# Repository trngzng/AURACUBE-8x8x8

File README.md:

# AURACUBE-8x8x8
RGB LED CUBE 8X8X8

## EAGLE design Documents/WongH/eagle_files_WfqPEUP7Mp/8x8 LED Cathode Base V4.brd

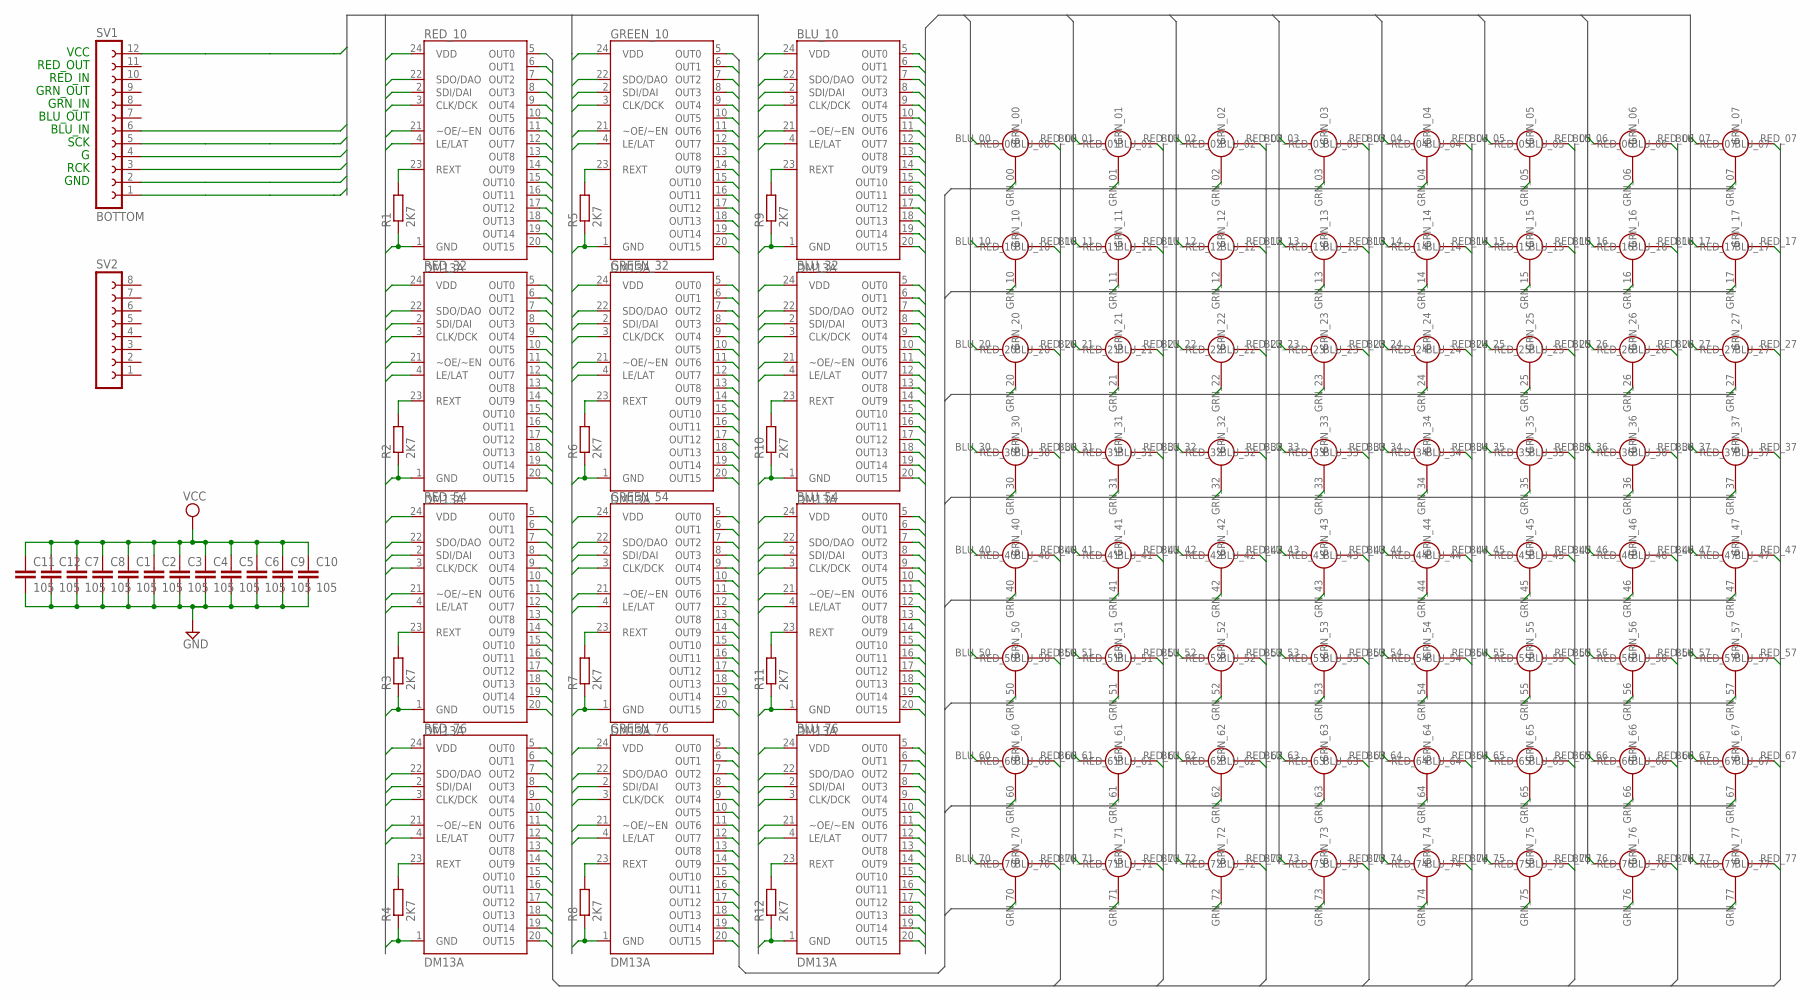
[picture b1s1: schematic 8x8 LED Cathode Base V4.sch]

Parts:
BLU_10, BLU_32, BLU_54, BLU_76: DM13A; DIL24-3
C1, C2, C3, C4, C5, C6, C7, C8, C9, C10, C11, C12: 105; C1206
GREEN_10, GREEN_32, GREEN_54, GREEN_76: DM13A; DIL24-3
R1, R2, R3, R4, R5, R6, R7, R8, R9, R10, R11, R12: 2K7; R1206
RED_10, RED_32, RED_54, RED_76: DM13A; DIL24-3
SV1: BOTTOM; FE12
SV2: FE08-1; FE08
U$1: 8X8_RGB_COLUMN; 8X8_RGB_LED_120

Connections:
BLANK: BLU_10.21 (~OE/~EN), BLU_32.21 (~OE/~EN), BLU_54.21 (~OE/~EN), BLU_76.21 (~OE/~EN), GREEN_10.21 (~OE/~EN), GREEN_32.21 (~OE/~EN), GREEN_54.21 (~OE/~EN), GREEN_76.21 (~OE/~EN), RED_10.21 (~OE/~EN), RED_32.21 (~OE/~EN), RED_54.21 (~OE/~EN), RED_76.21 (~OE/~EN), SV1.4
BLU_00: BLU_10.5 (OUT0), U$1.BLU_00
BLU_01: BLU_10.6 (OUT1), U$1.BLU_01
BLU_02: BLU_10.7 (OUT2), U$1.BLU_02
BLU_03: BLU_10.8 (OUT3), U$1.BLU_03
BLU_04: BLU_10.9 (OUT4), U$1.BLU_04
BLU_05: BLU_10.10 (OUT5), U$1.BLU_05
BLU_06: BLU_10.11 (OUT6), U$1.BLU_06
BLU_07: BLU_10.12 (OUT7), U$1.BLU_07
BLU_10: BLU_10.13 (OUT8), U$1.BLU_10
BLU_11: BLU_10.14 (OUT9), U$1.BLU_11
BLU_12: BLU_10.15 (OUT10), U$1.BLU_12
BLU_13: BLU_10.16 (OUT11), U$1.BLU_13
BLU_14: BLU_10.17 (OUT12), U$1.BLU_14
BLU_15: BLU_10.18 (OUT13), U$1.BLU_15
BLU_16: BLU_10.19 (OUT14), U$1.BLU_16
BLU_17: BLU_10.20 (OUT15), U$1.BLU_17
BLU_20: BLU_32.5 (OUT0), U$1.BLU_20
BLU_21: BLU_32.6 (OUT1), U$1.BLU_21
BLU_22: BLU_32.7 (OUT2), U$1.BLU_22
BLU_23: BLU_32.8 (OUT3), U$1.BLU_23
BLU_24: BLU_32.9 (OUT4), U$1.BLU_24
BLU_25: BLU_32.10 (OUT5), U$1.BLU_25
BLU_26: BLU_32.11 (OUT6), U$1.BLU_26
BLU_27: BLU_32.12 (OUT7), U$1.BLU_27
BLU_30: BLU_32.13 (OUT8), U$1.BLU_30
BLU_31: BLU_32.14 (OUT9), U$1.BLU_31
BLU_32: BLU_32.15 (OUT10), U$1.BLU_32
BLU_32_DATA: BLU_10.22 (SDO/DAO), BLU_32.2 (SDI/DAI)
BLU_33: BLU_32.16 (OUT11), U$1.BLU_33
BLU_34: BLU_32.17 (OUT12), U$1.BLU_34
BLU_35: BLU_32.18 (OUT13), U$1.BLU_35
BLU_36: BLU_32.19 (OUT14), U$1.BLU_36
BLU_37: BLU_32.20 (OUT15), U$1.BLU_37
BLU_40: BLU_54.5 (OUT0), U$1.BLU_40
BLU_41: BLU_54.6 (OUT1), U$1.BLU_41
BLU_42: BLU_54.7 (OUT2), U$1.BLU_42
BLU_43: BLU_54.8 (OUT3), U$1.BLU_43
BLU_44: BLU_54.9 (OUT4), U$1.BLU_44
BLU_45: BLU_54.10 (OUT5), U$1.BLU_45
BLU_46: BLU_54.11 (OUT6), U$1.BLU_46
BLU_47: BLU_54.12 (OUT7), U$1.BLU_47
BLU_50: BLU_54.13 (OUT8), U$1.BLU_50
BLU_51: BLU_54.14 (OUT9), U$1.BLU_51
BLU_52: BLU_54.15 (OUT10), U$1.BLU_52
BLU_53: BLU_54.16 (OUT11), U$1.BLU_53
BLU_54: BLU_54.17 (OUT12), U$1.BLU_54
BLU_54_DATA: BLU_32.22 (SDO/DAO), BLU_54.2 (SDI/DAI)
BLU_55: BLU_54.18 (OUT13), U$1.BLU_55
BLU_56: BLU_54.19 (OUT14), U$1.BLU_56
BLU_57: BLU_54.20 (OUT15), U$1.BLU_57
BLU_60: BLU_76.5 (OUT0), U$1.BLU_60
BLU_61: BLU_76.6 (OUT1), U$1.BLU_61
BLU_62: BLU_76.7 (OUT2), U$1.BLU_62
BLU_63: BLU_76.8 (OUT3), U$1.BLU_63
BLU_64: BLU_76.9 (OUT4), U$1.BLU_64
BLU_65: BLU_76.10 (OUT5), U$1.BLU_65
BLU_66: BLU_76.11 (OUT6), U$1.BLU_66
BLU_67: BLU_76.12 (OUT7), U$1.BLU_67
BLU_70: BLU_76.13 (OUT8), U$1.BLU_70
BLU_71: BLU_76.14 (OUT9), U$1.BLU_71
BLU_72: BLU_76.15 (OUT10), U$1.BLU_72
BLU_73: BLU_76.16 (OUT11), U$1.BLU_73
BLU_74: BLU_76.17 (OUT12), U$1.BLU_74
BLU_75: BLU_76.18 (OUT13), U$1.BLU_75
BLU_76: BLU_76.19 (OUT14), U$1.BLU_76
BLU_76_DATA: BLU_54.22 (SDO/DAO), BLU_76.2 (SDI/DAI)
BLU_77: BLU_76.20 (OUT15), U$1.BLU_77
BLU_IN: BLU_10.2 (SDI/DAI), SV1.6
BLU_OUT: BLU_76.22 (SDO/DAO), GREEN_10.2 (SDI/DAI)
CLOCK: BLU_10.3 (CLK/DCK), BLU_32.3 (CLK/DCK), BLU_54.3 (CLK/DCK), BLU_76.3 (CLK/DCK), GREEN_10.3 (CLK/DCK), GREEN_32.3 (CLK/DCK), GREEN_54.3 (CLK/DCK), GREEN_76.3 (CLK/DCK), RED_10.3 (CLK/DCK), RED_32.3 (CLK/DCK), RED_54.3 (CLK/DCK), RED_76.3 (CLK/DCK), SV1.5
GND: BLU_10.1 (GND), BLU_32.1 (GND), BLU_54.1 (GND), BLU_76.1 (GND), C1.2, C2.2, C3.2, C4.2, C5.2, C6.2, C7.2, C8.2, C9.2, C10.2, C11.2, C12.2, GREEN_10.1 (GND), GREEN_32.1 (GND), GREEN_54.1 (GND), GREEN_76.1 (GND), R1.1, R2.1, R3.1, R4.1, R5.1, R6.1, R7.1, R8.1, R9.1, R10.1, R11.1, R12.1, RED_10.1 (GND), RED_32.1 (GND), RED_54.1 (GND), RED_76.1 (GND), SV1.1, SV1.2
GRN_00: GREEN_10.5 (OUT0), U$1.GRN_00
GRN_01: GREEN_10.6 (OUT1), U$1.GRN_01
GRN_02: GREEN_10.7 (OUT2), U$1.GRN_02
GRN_03: GREEN_10.8 (OUT3), U$1.GRN_03
GRN_04: GREEN_10.9 (OUT4), U$1.GRN_04
GRN_05: GREEN_10.10 (OUT5), U$1.GRN_05
GRN_06: GREEN_10.11 (OUT6), U$1.GRN_06
GRN_07: GREEN_10.12 (OUT7), U$1.GRN_07
GRN_10: GREEN_10.13 (OUT8), U$1.GRN_10
GRN_11: GREEN_10.14 (OUT9), U$1.GRN_11
GRN_12: GREEN_10.15 (OUT10), U$1.GRN_12
GRN_13: GREEN_10.16 (OUT11), U$1.GRN_13
GRN_14: GREEN_10.17 (OUT12), U$1.GRN_14
GRN_15: GREEN_10.18 (OUT13), U$1.GRN_15
GRN_16: GREEN_10.19 (OUT14), U$1.GRN_16
GRN_17: GREEN_10.20 (OUT15), U$1.GRN_17
GRN_20: GREEN_32.5 (OUT0), U$1.GRN_20
GRN_21: GREEN_32.6 (OUT1), U$1.GRN_21
GRN_22: GREEN_32.7 (OUT2), U$1.GRN_22
GRN_23: GREEN_32.8 (OUT3), U$1.GRN_23
GRN_24: GREEN_32.9 (OUT4), U$1.GRN_24
GRN_25: GREEN_32.10 (OUT5), U$1.GRN_25
GRN_26: GREEN_32.11 (OUT6), U$1.GRN_26
GRN_27: GREEN_32.12 (OUT7), U$1.GRN_27
GRN_30: GREEN_32.13 (OUT8), U$1.GRN_30
GRN_31: GREEN_32.14 (OUT9), U$1.GRN_31
GRN_32: GREEN_32.15 (OUT10), U$1.GRN_32
GRN_32_DATA: GREEN_10.22 (SDO/DAO), GREEN_32.2 (SDI/DAI)
GRN_33: GREEN_32.16 (OUT11), U$1.GRN_33
GRN_34: GREEN_32.17 (OUT12), U$1.GRN_34
GRN_35: GREEN_32.18 (OUT13), U$1.GRN_35
GRN_36: GREEN_32.19 (OUT14), U$1.GRN_36
GRN_37: GREEN_32.20 (OUT15), U$1.GRN_37
GRN_40: GREEN_54.5 (OUT0), U$1.GRN_40
GRN_41: GREEN_54.6 (OUT1), U$1.GRN_41
GRN_42: GREEN_54.7 (OUT2), U$1.GRN_42
GRN_43: GREEN_54.8 (OUT3), U$1.GRN_43
GRN_44: GREEN_54.9 (OUT4), U$1.GRN_44
GRN_45: GREEN_54.10 (OUT5), U$1.GRN_45
GRN_46: GREEN_54.11 (OUT6), U$1.GRN_46
GRN_47: GREEN_54.12 (OUT7), U$1.GRN_47
GRN_50: GREEN_54.13 (OUT8), U$1.GRN_50
GRN_51: GREEN_54.14 (OUT9), U$1.GRN_51
GRN_52: GREEN_54.15 (OUT10), U$1.GRN_52
GRN_53: GREEN_54.16 (OUT11), U$1.GRN_53
GRN_54: GREEN_54.17 (OUT12), U$1.GRN_54
GRN_54_DATA: GREEN_32.22 (SDO/DAO), GREEN_54.2 (SDI/DAI)
GRN_55: GREEN_54.18 (OUT13), U$1.GRN_55
GRN_56: GREEN_54.19 (OUT14), U$1.GRN_56
GRN_57: GREEN_54.20 (OUT15), U$1.GRN_57
GRN_60: GREEN_76.5 (OUT0), U$1.GRN_60
GRN_61: GREEN_76.6 (OUT1), U$1.GRN_61
GRN_62: GREEN_76.7 (OUT2), U$1.GRN_62
GRN_63: GREEN_76.8 (OUT3), U$1.GRN_63
GRN_64: GREEN_76.9 (OUT4), U$1.GRN_64
GRN_65: GREEN_76.10 (OUT5), U$1.GRN_65
GRN_66: GREEN_76.11 (OUT6), U$1.GRN_66
GRN_67: GREEN_76.12 (OUT7), U$1.GRN_67
GRN_70: GREEN_76.13 (OUT8), U$1.GRN_70
GRN_71: GREEN_76.14 (OUT9), U$1.GRN_71
GRN_72: GREEN_76.15 (OUT10), U$1.GRN_72
GRN_73: GREEN_76.16 (OUT11), U$1.GRN_73
GRN_74: GREEN_76.17 (OUT12), U$1.GRN_74
GRN_75: GREEN_76.18 (OUT13), U$1.GRN_75
GRN_76: GREEN_76.19 (OUT14), U$1.GRN_76
GRN_76_DATA: GREEN_54.22 (SDO/DAO), GREEN_76.2 (SDI/DAI)
GRN_77: GREEN_76.20 (OUT15), U$1.GRN_77
GRN_OUT: GREEN_76.22 (SDO/DAO), RED_10.2 (SDI/DAI)
LATCH: BLU_10.4 (LE/LAT), BLU_32.4 (LE/LAT), BLU_54.4 (LE/LAT), BLU_76.4 (LE/LAT), GREEN_10.4 (LE/LAT), GREEN_32.4 (LE/LAT), GREEN_54.4 (LE/LAT), GREEN_76.4 (LE/LAT), RED_10.4 (LE/LAT), RED_32.4 (LE/LAT), RED_54.4 (LE/LAT), RED_76.4 (LE/LAT), SV1.3
unnamed: GREEN_10.23 (REXT), R5.2
unnamed: GREEN_32.23 (REXT), R6.2
unnamed: GREEN_54.23 (REXT), R7.2
unnamed: GREEN_76.23 (REXT), R8.2
unnamed: BLU_10.23 (REXT), R9.2
unnamed: BLU_32.23 (REXT), R10.2
unnamed: BLU_54.23 (REXT), R11.2
unnamed: BLU_76.23 (REXT), R12.2
unnamed: R1.2, RED_10.23 (REXT)
unnamed: R2.2, RED_32.23 (REXT)
unnamed: R3.2, RED_54.23 (REXT)
unnamed: R4.2, RED_76.23 (REXT)
RED_00: RED_10.5 (OUT0), U$1.RED_00
RED_01: RED_10.6 (OUT1), U$1.RED_01
RED_02: RED_10.7 (OUT2), U$1.RED_02
RED_03: RED_10.8 (OUT3), U$1.RED_03
RED_04: RED_10.9 (OUT4), U$1.RED_04
RED_05: RED_10.10 (OUT5), U$1.RED_05
RED_06: RED_10.11 (OUT6), U$1.RED_06
RED_07: RED_10.12 (OUT7), U$1.RED_07
RED_10: RED_10.13 (OUT8), U$1.RED_10
RED_11: RED_10.14 (OUT9), U$1.RED_11
RED_12: RED_10.15 (OUT10), U$1.RED_12
RED_13: RED_10.16 (OUT11), U$1.RED_13
RED_14: RED_10.17 (OUT12), U$1.RED_14
RED_15: RED_10.18 (OUT13), U$1.RED_15
RED_16: RED_10.19 (OUT14), U$1.RED_16
RED_17: RED_10.20 (OUT15), U$1.RED_17
RED_20: RED_32.5 (OUT0), U$1.RED_20
RED_21: RED_32.6 (OUT1), U$1.RED_21
RED_22: RED_32.7 (OUT2), U$1.RED_22
RED_23: RED_32.8 (OUT3), U$1.RED_23
RED_24: RED_32.9 (OUT4), U$1.RED_24
RED_25: RED_32.10 (OUT5), U$1.RED_25
RED_26: RED_32.11 (OUT6), U$1.RED_26
RED_27: RED_32.12 (OUT7), U$1.RED_27
RED_30: RED_32.13 (OUT8), U$1.RED_30
RED_31: RED_32.14 (OUT9), U$1.RED_31
RED_32: RED_32.15 (OUT10), U$1.RED_32
RED_32_DATA: RED_10.22 (SDO/DAO), RED_32.2 (SDI/DAI)
RED_33: RED_32.16 (OUT11), U$1.RED_33
RED_34: RED_32.17 (OUT12), U$1.RED_34
RED_35: RED_32.18 (OUT13), U$1.RED_35
RED_36: RED_32.19 (OUT14), U$1.RED_36
RED_37: RED_32.20 (OUT15), U$1.RED_37
RED_40: RED_54.5 (OUT0), U$1.RED_40
RED_41: RED_54.6 (OUT1), U$1.RED_41
RED_42: RED_54.7 (OUT2), U$1.RED_42
RED_43: RED_54.8 (OUT3), U$1.RED_43
RED_44: RED_54.9 (OUT4), U$1.RED_44
RED_45: RED_54.10 (OUT5), U$1.RED_45
RED_46: RED_54.11 (OUT6), U$1.RED_46
RED_47: RED_54.12 (OUT7), U$1.RED_47
RED_50: RED_54.13 (OUT8), U$1.RED_50
RED_51: RED_54.14 (OUT9), U$1.RED_51
RED_52: RED_54.15 (OUT10), U$1.RED_52
RED_53: RED_54.16 (OUT11), U$1.RED_53
RED_54: RED_54.17 (OUT12), U$1.RED_54
RED_54_DATA: RED_32.22 (SDO/DAO), RED_54.2 (SDI/DAI)
RED_55: RED_54.18 (OUT13), U$1.RED_55
RED_56: RED_54.19 (OUT14), U$1.RED_56
RED_57: RED_54.20 (OUT15), U$1.RED_57
RED_60: RED_76.5 (OUT0), U$1.RED_60
RED_61: RED_76.6 (OUT1), U$1.RED_61
RED_62: RED_76.7 (OUT2), U$1.RED_62
RED_63: RED_76.8 (OUT3), U$1.RED_63
RED_64: RED_76.9 (OUT4), U$1.RED_64
RED_65: RED_76.10 (OUT5), U$1.RED_65
RED_66: RED_76.11 (OUT6), U$1.RED_66
RED_67: RED_76.12 (OUT7), U$1.RED_67
RED_70: RED_76.13 (OUT8), U$1.RED_70
RED_71: RED_76.14 (OUT9), U$1.RED_71
RED_72: RED_76.15 (OUT10), U$1.RED_72
RED_73: RED_76.16 (OUT11), U$1.RED_73
RED_74: RED_76.17 (OUT12), U$1.RED_74
RED_75: RED_76.18 (OUT13), U$1.RED_75
RED_76: RED_76.19 (OUT14), U$1.RED_76
RED_76_DATA: RED_54.22 (SDO/DAO), RED_76.2 (SDI/DAI)
RED_77: RED_76.20 (OUT15), U$1.RED_77
RED_OUT: RED_76.22 (SDO/DAO)
VCC: BLU_10.24 (VDD), BLU_32.24 (VDD), BLU_54.24 (VDD), BLU_76.24 (VDD), C1.1, C2.1, C3.1, C4.1, C5.1, C6.1, C7.1, C8.1, C9.1, C10.1, C11.1, C12.1, GREEN_10.24 (VDD), GREEN_32.24 (VDD), GREEN_54.24 (VDD), GREEN_76.24 (VDD), RED_10.24 (VDD), RED_32.24 (VDD), RED_54.24 (VDD), RED_76.24 (VDD), SV1.12

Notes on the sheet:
BLU_IN
GRN_IN
RED_IN
SCK
RCK
GND
VCC
BLU_OUT
GRN_OUT
RED_OUT

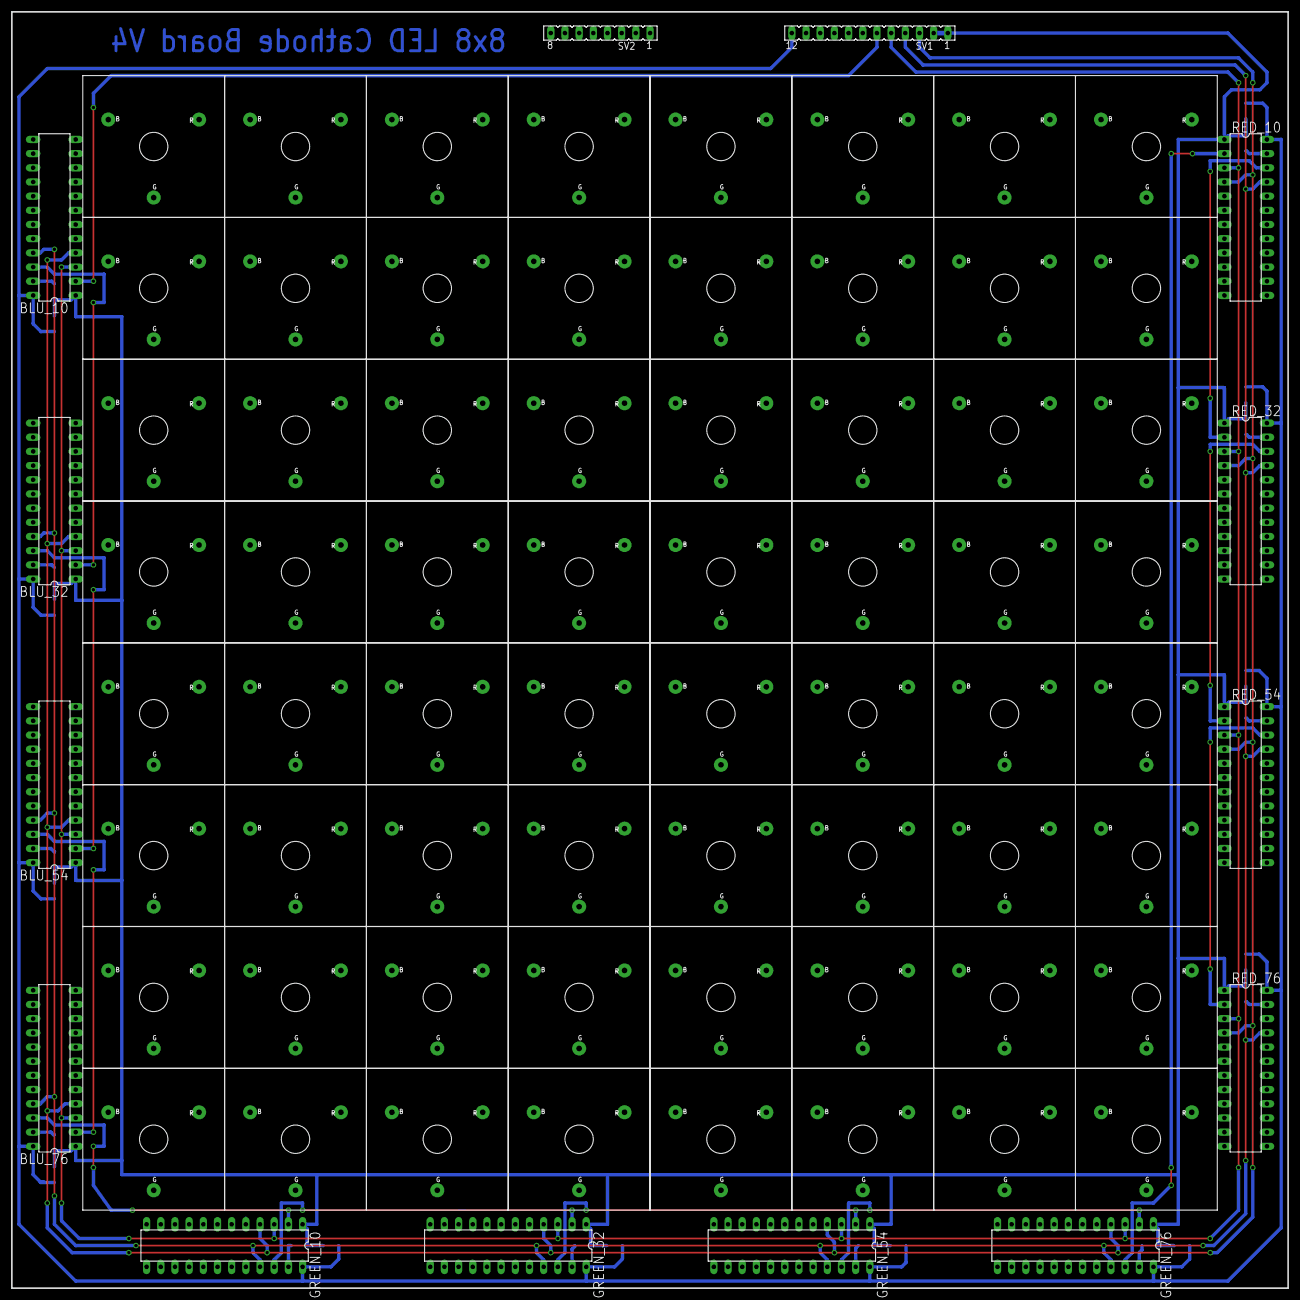
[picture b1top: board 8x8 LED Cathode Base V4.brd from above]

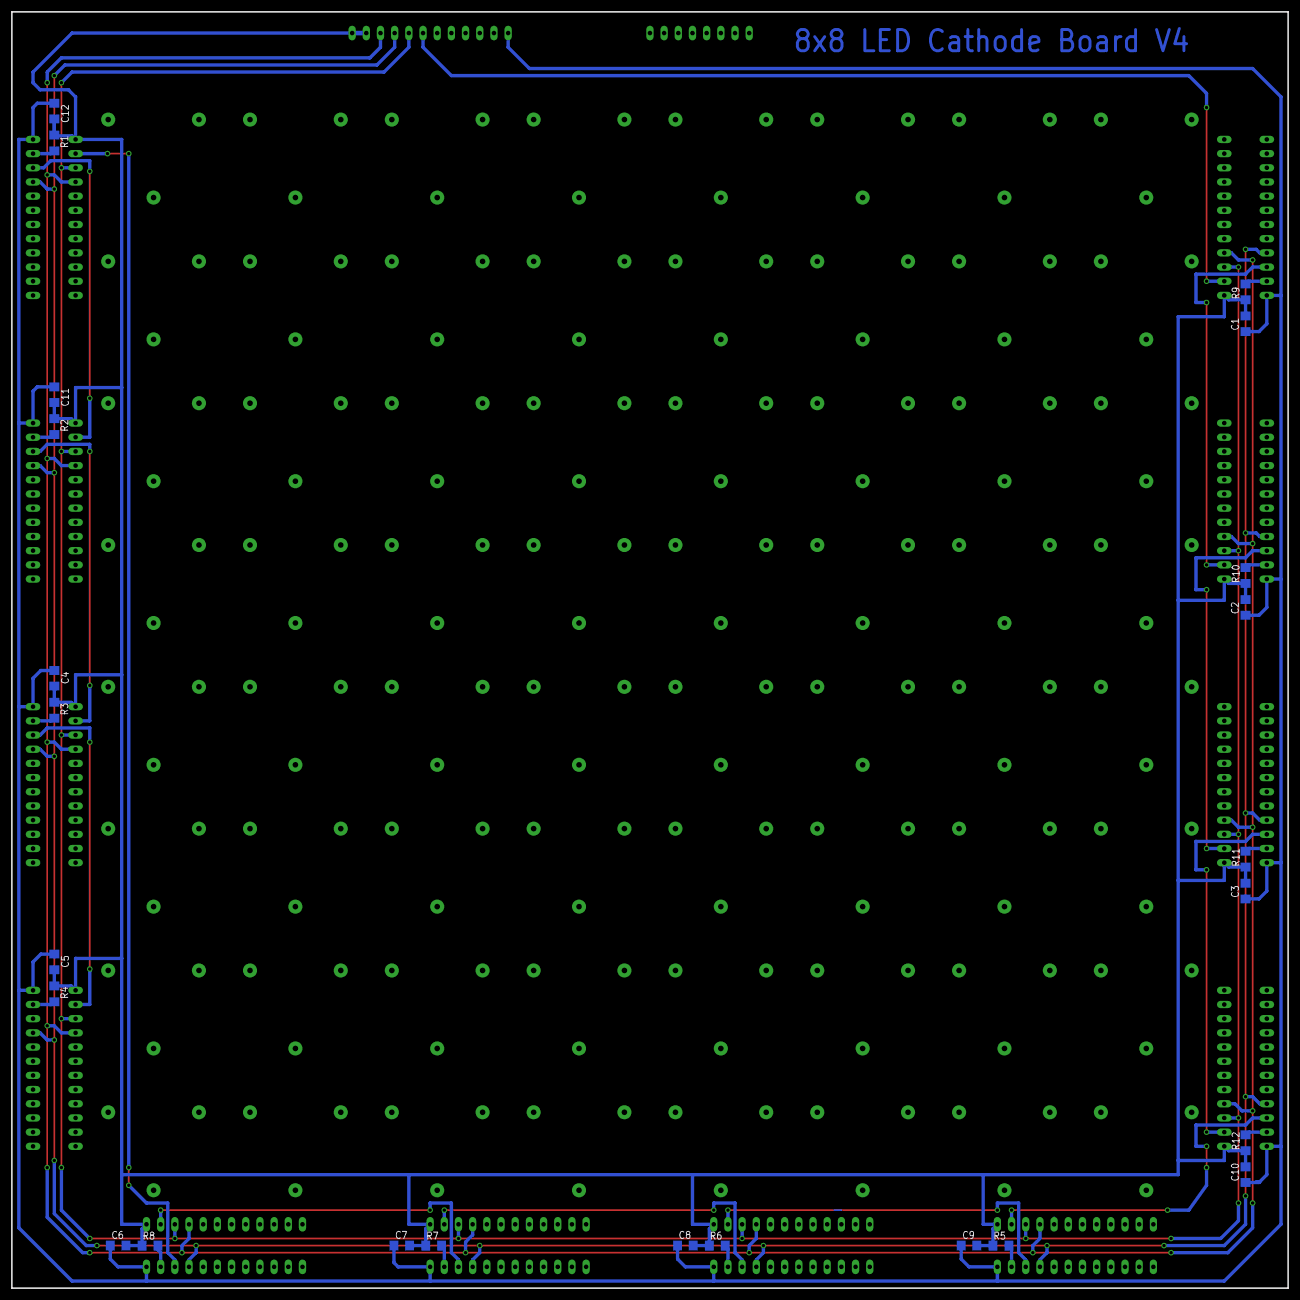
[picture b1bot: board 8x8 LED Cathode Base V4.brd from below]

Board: 2 copper layers, 228.6 x 228.6 mm, 39 parts (24 on the bottom side), 221 nets.

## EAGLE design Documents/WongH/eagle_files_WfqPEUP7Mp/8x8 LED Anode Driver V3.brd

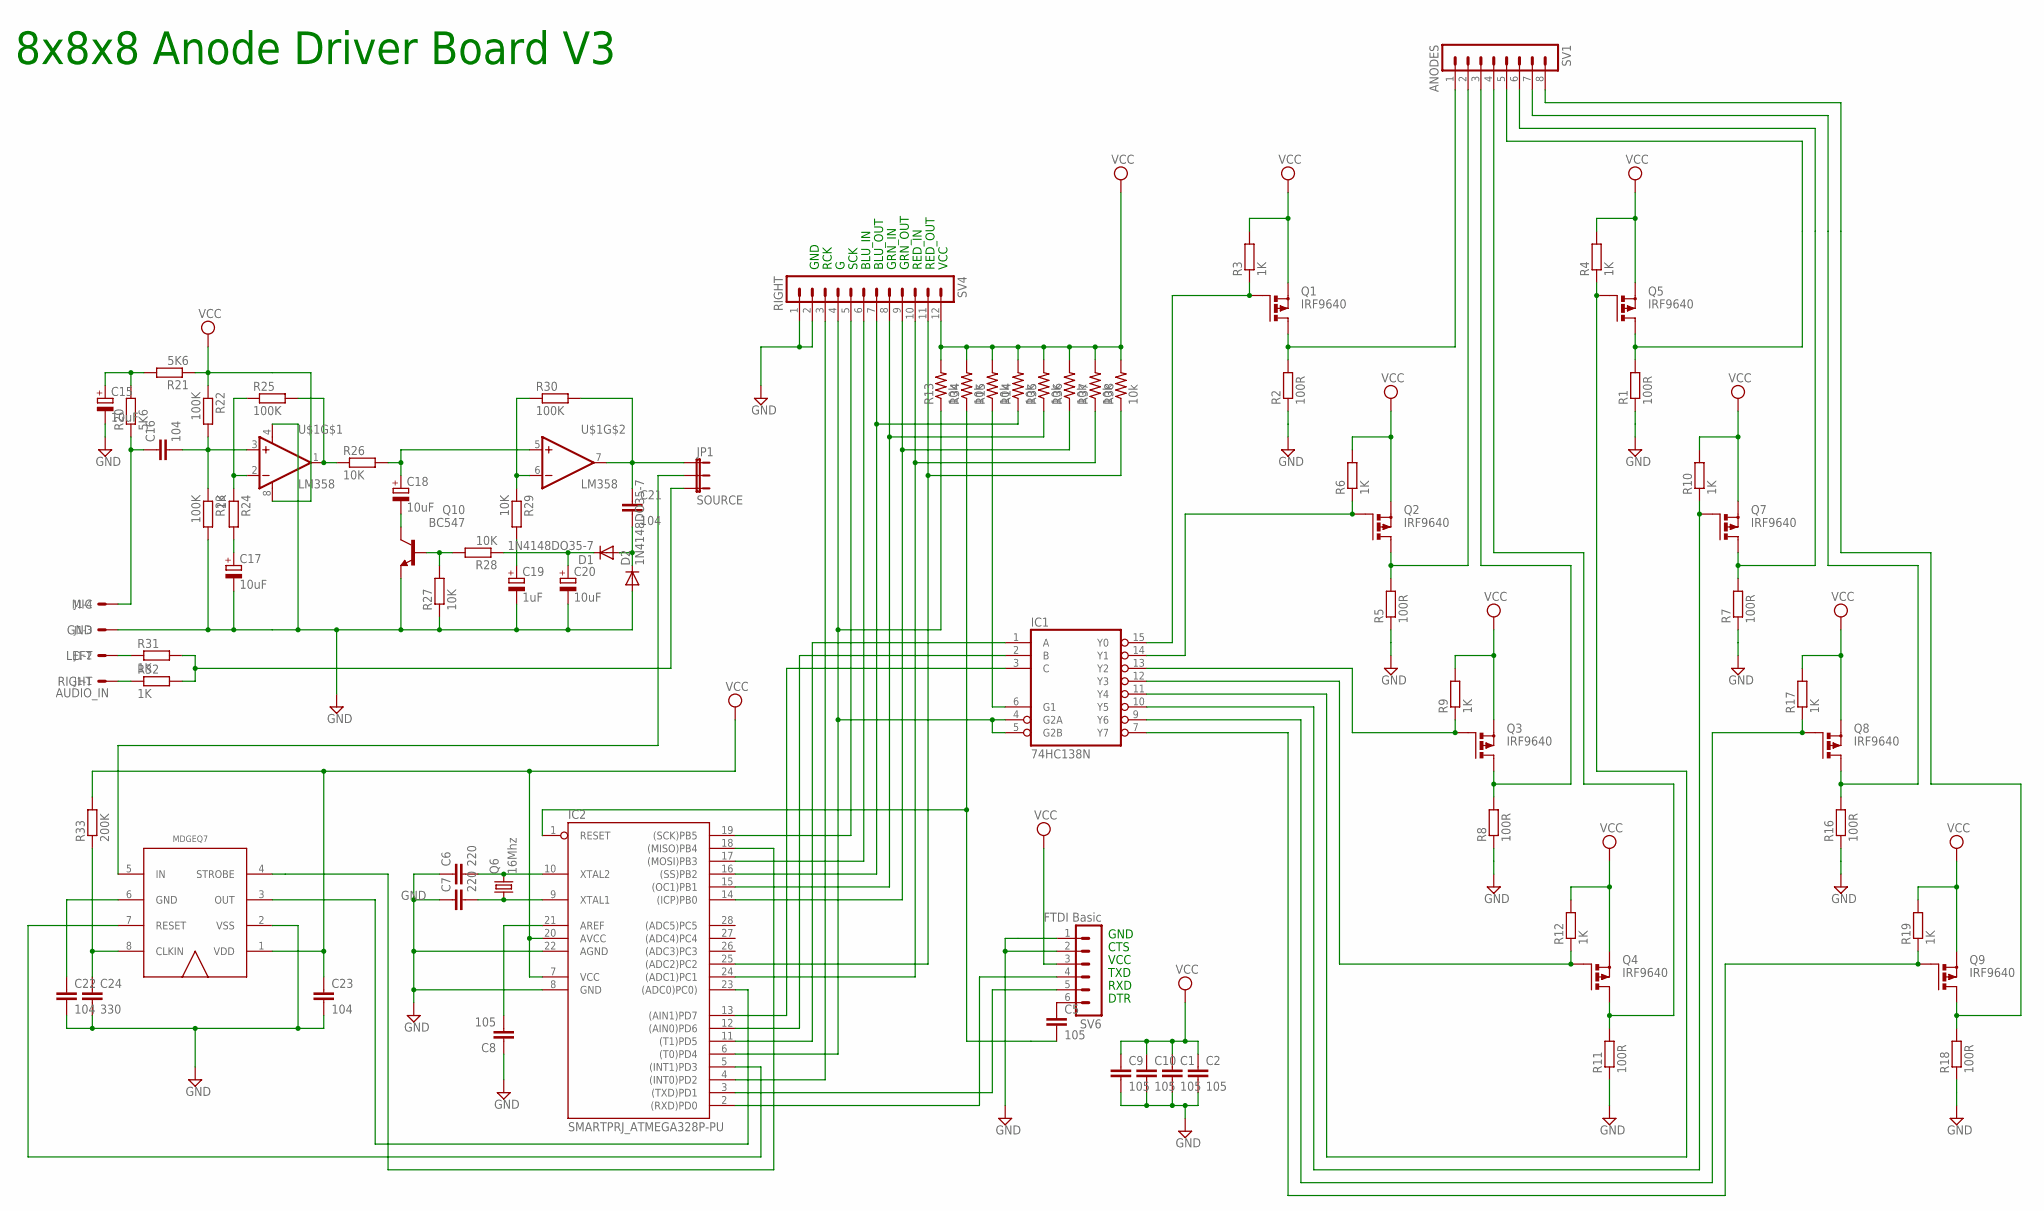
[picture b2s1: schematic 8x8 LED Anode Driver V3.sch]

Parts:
C1, C2, C10: 105; C025-030X050
C5: 105; C050-025X075
C6, C7: 220; C050-025X075
C8, C9: 105; C025-025X050
C15, C17, C18, C20: 10uF; E2,5-5
C16, C21: 104; C050-030X075
C19: 1uF; E2,5-5
C22, C23: 104; C025-030X050
C24: 330; C050-030X075
D1, D2: 1N4148DO35-7; DO35-7
IC1: 74HC138N; DIL16
IC2: SMARTPRJ_ATMEGA328P-PU; SMARTPRJ_DIL28-3
J1: AUDIO_IN; 7395-04
JP1: SOURCE; 1X03
Q1, Q2, Q3, Q4, Q5, Q7, Q8, Q9: IRF9640; TO220BH_NO_HOLE
Q6: 16Mhz; HC49/S
Q10: BC547; TO92
R1, R2, R5, R7, R8, R11, R16, R18: 100R; 0207/10
R3, R4, R6, R9, R10, R12, R17, R19, R24, R31, R32: 1K; 0207/10
R13, R14, R15, R34, R35, R36, R37, R38: 10k; 0207/10
R20, R21: 5K6; 0207/10
R22, R23, R25, R30: 100K; 0207/10
R26, R27, R28, R29: 10K; 0207/10
R33: 200K; 0207/10
SV1: ANODES; MA08-1W
SV4: RIGHT; MA12-1W
SV6: FTDI Basic; MA06-1
U$1: LM358; DIP08
U$2: MSGEQ7; DIL08

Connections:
BLANK: IC1.4 (G2A), IC1.5 (G2B), IC2.6 ((T0)PD4), R13.1, SV4.4
DRAIN_0: Q1.D, R2.2, SV1.1
DRAIN_1: Q2.D, R5.2, SV1.2
DRAIN_2: Q3.D, R8.2, SV1.3
DRAIN_3: Q4.D, R11.2, SV1.4
DRAIN_4: Q5.D, R1.2, SV1.5
DRAIN_5: Q7.D, R7.2, SV1.6
DRAIN_6: Q8.D, R16.2, SV1.7
DRAIN_7: Q9.D, R18.2, SV1.8
GND: C1.2, C2.2, C6.1, C7.1, C8.1, C9.2, C10.2, C15.-, C17.-, C19.-, C20.-, C22.2, C23.2, C24.2, D2.A, IC1.8 (GND), IC2.8 (GND), IC2.22 (AGND), J1.3, Q10.1 (E), R1.1, R2.1, R5.1, R7.1, R8.1, R11.1, R16.1, R18.1, R23.2, R27.1, SV4.1, SV4.2, SV6.1, SV6.2, U$1.4 (V-), U$2.2 (VSS)
LATCH: IC2.4 ((INT0)PD2), SV4.3
MSGEQ7_OUT: IC2.23 ((ADC0)PC0)), U$2.3 (OUT)
MSGEQ7_RESET: IC2.5 ((INT1)PD3), U$2.7 (RESET)
MSGEQ7_STROBE: IC2.18 ((MISO)PB4), U$2.4 (STROBE)
unnamed: IC2.16 ((SS)PB2), R14.1, SV4.7
unnamed: IC1.11 (Y4), Q5.G, R4.1
unnamed: IC1.15 (Y0), Q1.G, R3.1
unnamed: IC1.10 (Y5), Q7.G, R10.1
unnamed: IC1.2 (B), IC2.12 ((AIN0)PD6)
unnamed: IC1.14 (Y1), Q2.G, R6.1
unnamed: C15.+, R20.2, R21.2
unnamed: IC1.3 (C), IC2.13 ((AIN1)PD7)
unnamed: IC1.13 (Y2), Q3.G, R9.1
unnamed: IC1.9 (Y6), Q8.G, R17.1
unnamed: IC1.7 (Y7), Q9.G, R19.1
unnamed: IC1.12 (Y3), Q4.G, R12.1
unnamed: C16.1, J1.4, R20.1
unnamed: C16.2, R22.2, R23.1, U$1.3 (+IN)
unnamed: R24.1, R25.1, U$1.2 (-IN)
unnamed: C17.+, R24.2
unnamed: J1.2, R31.1
unnamed: J1.1, R32.1
unnamed: JP1.3, R31.2, R32.2
unnamed: R25.2, R26.1, U$1.1 (OUT)
unnamed: C18.+, R26.2, U$1.5 (+IN)
unnamed: R29.1, R30.1, U$1.6 (-IN)
unnamed: Q10.2 (B), R27.2, R28.2
unnamed: C18.-, Q10.3 (C)
unnamed: C19.+, R29.2
unnamed: IC2.2 ((RXD)PD0), SV6.4
unnamed: IC2.3 ((TXD)PD1), SV6.5
unnamed: IC2.19 ((SCK)PB5), SV4.5
unnamed: C20.+, D1.C, R28.1
unnamed: IC2.15 ((OC1)PB1), R35.1, SV4.8
unnamed: C7.2, IC2.9 (XTAL1), Q6.1
unnamed: C6.2, IC2.10 (XTAL2), Q6.2
unnamed: C8.2, IC2.21 (AREF)
unnamed: C5.2, IC2.1 (RESET), R34.1
unnamed: IC2.17 ((MOSI)PB3), SV4.6
unnamed: C5.1, SV6.6
unnamed: IC1.1 (A), IC2.11 ((T1)PD5)
unnamed: IC1.6 (G1), R15.1
unnamed: C21.2, D1.A, D2.C
unnamed: C21.1, JP1.1, R30.2, U$1.7 (OUT)
unnamed: JP1.2, U$2.5 (IN)
unnamed: C22.1, U$2.6 (GND)
unnamed: C24.1, R33.1, U$2.8 (CLKIN)
unnamed: IC2.14 ((ICP)PB0), R36.1, SV4.9
unnamed: IC2.24 ((ADC1)PC1), R37.1, SV4.10
unnamed: IC2.25 ((ADC2)PC2), R38.1, SV4.11
VCC: C1.1, C2.1, C9.1, C10.1, C23.1, IC1.16 (VCC), IC2.7 (VCC), IC2.20 (AVCC), Q1.S, Q2.S, Q3.S, Q4.S, Q5.S, Q7.S, Q8.S, Q9.S, R3.2, R4.2, R6.2, R9.2, R10.2, R12.2, R13.2, R14.2, R15.2, R17.2, R19.2, R21.1, R22.1, R33.2, R34.2, R35.2, R36.2, R37.2, R38.2, SV4.12, SV6.3, U$1.8 (V+), U$2.1 (VDD)

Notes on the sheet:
GND
CTS
VCC
TXD
RXD
DTR
BLU_IN
GRN_IN
RED_IN
SCK
RCK
BLU_OUT
GRN_OUT
RED_OUT
MIC
LEFT
RIGHT
8x8x8 Anode Driver Board V3

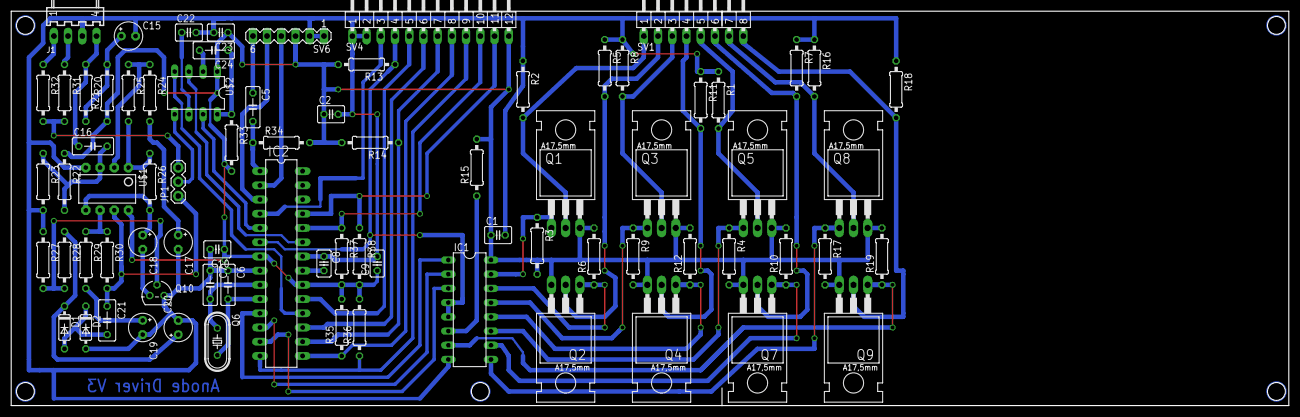
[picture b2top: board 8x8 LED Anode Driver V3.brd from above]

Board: 2 copper layers, 228.3 x 70.5 mm, 77 parts (0 on the bottom side), 61 nets.

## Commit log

2023-01-04 "test ic"
2023-01-20 testboard + mcu schematic
2023-01-27 update pcd

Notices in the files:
parts and their libraries:
SparkFun-AnalogIC: Licensing: CC v3.0 Share-Alike You are welcome to use this library for commercial purposes.
